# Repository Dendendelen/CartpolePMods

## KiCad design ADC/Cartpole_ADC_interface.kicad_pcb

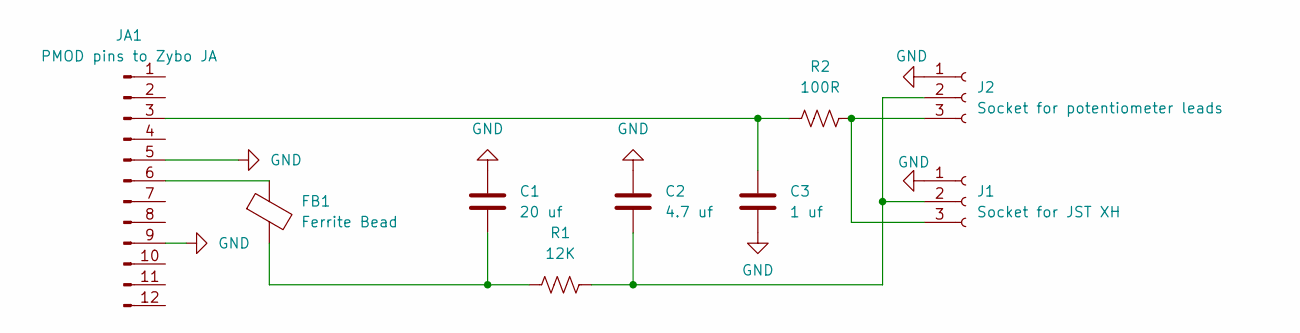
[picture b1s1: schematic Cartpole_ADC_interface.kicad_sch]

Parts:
C1: 20 uf; C_1206_3216Metric_Pad1.33x1.80mm_HandSolder
C2: 4.7 uf; C_1206_3216Metric_Pad1.33x1.80mm_HandSolder
C3: 1 uf; C_1206_3216Metric_Pad1.33x1.80mm_HandSolder
FB1: Ferrite Bead; C_1206_3216Metric_Pad1.33x1.80mm_HandSolder
J1: Socket for JST XH; JST_XH_B3B-XH-AM_1x03_P2.50mm_Vertical
J2: Socket for potentiometer leads; PinHeader_1x03_P2.54mm_Vertical
JA1: PMOD pins to Zybo JA; pmod_pin_array_6x2
R1: 12K; R_1206_3216Metric_Pad1.30x1.75mm_HandSolder
R2: 100R; R_1206_3216Metric_Pad1.30x1.75mm_HandSolder

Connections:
GND: C1.1, C2.1, C3.2, J1.1, J2.1, JA1.5, JA1.9
unnamed: C1.2, FB1.2, R1.2
unnamed: C2.2, J1.2, J2.2, R1.1
unnamed: J1.3, J2.3, R2.1
unnamed: C3.1, JA1.3, R2.2
unnamed: FB1.1, JA1.6

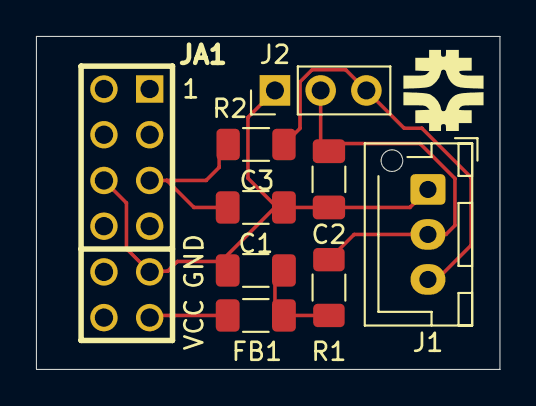
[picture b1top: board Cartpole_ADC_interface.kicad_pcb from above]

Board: 2 copper layers, 25.8 x 18.5 mm, 9 parts (0 on the bottom side), 6 nets.

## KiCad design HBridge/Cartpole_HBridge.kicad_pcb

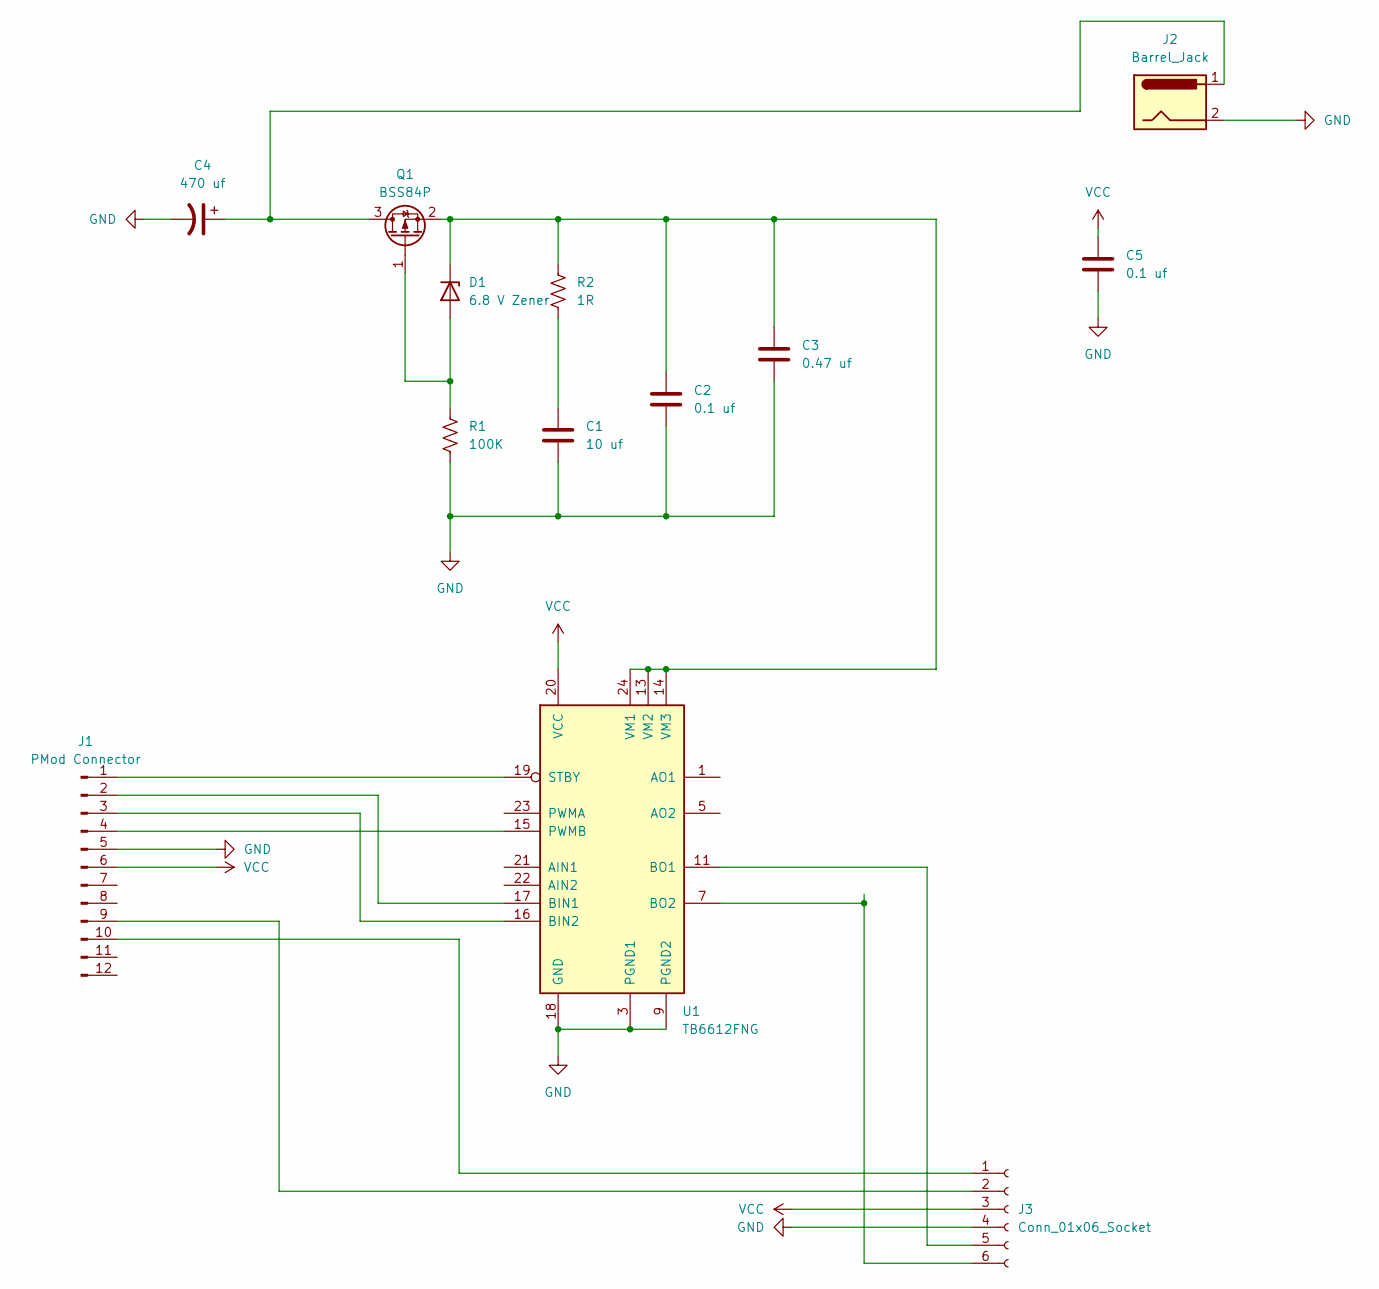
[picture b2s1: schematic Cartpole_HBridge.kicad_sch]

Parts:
C1: 10 uf; C_1206_3216Metric_Pad1.33x1.80mm_HandSolder
C2, C5: 0.1 uf; C_1206_3216Metric_Pad1.33x1.80mm_HandSolder
C3: 0.47 uf; C_1206_3216Metric_Pad1.33x1.80mm_HandSolder
C4: 470 uf; C_Elec_6.3x7.7
D1: 6.8 V Zener; D_SMB_Handsoldering
J1: PMod Connector; pmod_pin_array_6x2
J2: Barrel_Jack; PinHeader_2x01_P2.54mm_Vertical
J3: Conn_01x06_Socket; PinHeader_1x06_P2.54mm_Vertical
Q1: BSS84P; SOT-23_Handsoldering
R1: 100K; R_1206_3216Metric_Pad1.30x1.75mm_HandSolder
R2: 1R; R_1206_3216Metric_Pad1.30x1.75mm_HandSolder
U1: TB6612FNG; SSOP-24_5.3x8.2mm_P0.65mm

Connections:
GND: C1.2, C2.2, C3.2, C4.2, C5.2, J1.5, J2.2, J3.4, R1.2, U1.3 (PGND1), U1.4 (PGND1), U1.9 (PGND2), U1.10 (PGND2), U1.18 (GND)
unnamed: C1.1, R2.2
unnamed: D1.2 (A), Q1.1 (G), R1.1
unnamed: C2.1, C3.1, D1.1 (K), Q1.2 (S), R2.1, U1.13 (VM2), U1.14 (VM3), U1.24 (VM1)
unnamed: J1.1, U1.19 (STBY)
unnamed: J1.2, U1.17 (BIN1)
unnamed: J1.3, U1.16 (BIN2)
unnamed: J1.4, U1.15 (PWMB)
unnamed: J1.9, J3.2
unnamed: J1.10, J3.1
unnamed: J3.5, U1.11 (BO1), U1.12 (BO1)
unnamed: J3.6, U1.7 (BO2), U1.8 (BO2)
unnamed: C4.1, J2.1, Q1.3 (D)
unnamed: U1.1 (AO1), U1.2 (AO1)
unnamed: U1.5 (AO2), U1.6 (AO2)
VCC: C5.1, J1.6, J3.3, U1.20 (VCC)

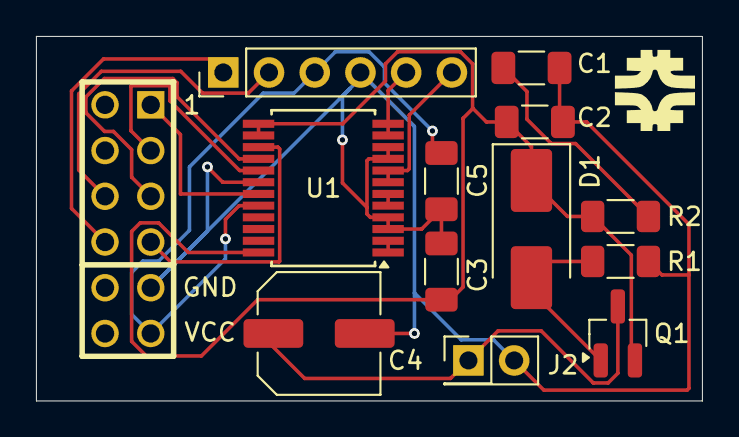
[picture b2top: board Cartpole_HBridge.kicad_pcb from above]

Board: 2 copper layers, 37.0 x 20.2 mm, 13 parts (0 on the bottom side), 16 nets.

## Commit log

2024-07-01 Schematics for the ADC interface and the HBridge interface
2024-07-01 Added drill files
2024-07-01 Upped the footprint size of the 470uf cap
2024-07-01 Changed 470uf cap to one more readily availible
2024-07-01 Compressed size of board to be within PMod spec
2024-07-01 Made the board somewhat smaller and more compressed
2024-07-02 Fit left size of ADC interface board to the PMOD spec
2024-07-10 Grounded pin 9 of the adc interface board (apparently this is atually necessary)
